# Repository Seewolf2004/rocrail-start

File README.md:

# rocrail-start
startet Rocrail auf einem Raspberry Pi 4B

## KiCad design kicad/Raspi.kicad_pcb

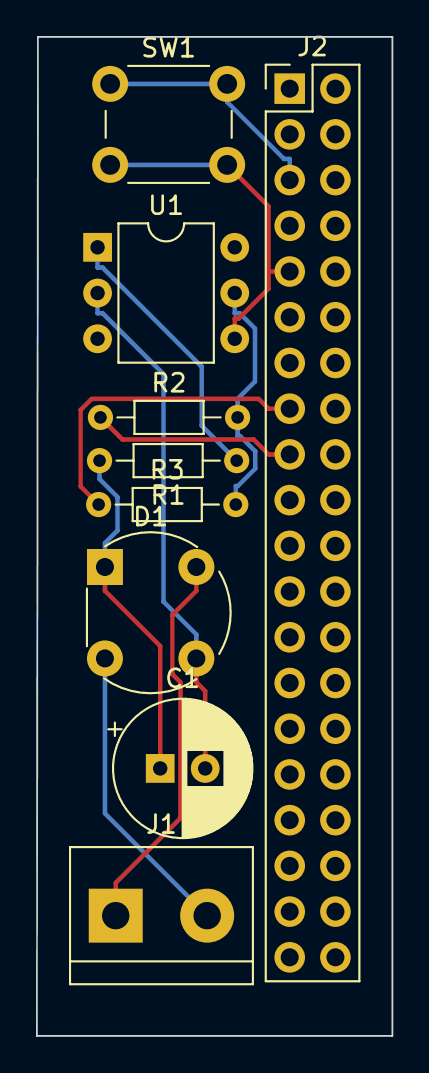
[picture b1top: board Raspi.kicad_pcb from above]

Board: 2 copper layers, 19.8 x 55.5 mm, 9 parts (0 on the bottom side), 10 nets.

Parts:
C1: 47 uF; CP_Radial_D7.5mm_P2.50mm
D1: D_Bridge_+A-A; Diode_Bridge_Round_D8.9mm
J1: Conn_01x02_Male; TerminalBlock_bornier-2_P5.08mm
J2: Raspberry_Pi_2_3; PinHeader_2x20_P2.54mm_Vertical
R1: 1,5k; R_Axial_DIN0204_L3.6mm_D1.6mm_P7.62mm_Horizontal
R2: 10k; R_Axial_DIN0204_L3.6mm_D1.6mm_P7.62mm_Horizontal
R3: 1k; R_Axial_DIN0204_L3.6mm_D1.6mm_P7.62mm_Horizontal
SW1: SW_Push; SW_PUSH_6mm_H4.3mm
U1: CNY17-4; DIP-6_W7.62mm

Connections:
/GPIO3: J2.5, SW1.1
unnamed: C1.1, D1.1, R1.2
unnamed: C1.2, D1.3, U1.2
unnamed: D1.2, J1.2
unnamed: D1.4, J1.1
unnamed: J2.9, SW1.2, U1.4
unnamed: J2.15, R3.1
unnamed: J2.17, R2.1
unnamed: R1.1, U1.1
unnamed: R2.2, R3.2, U1.5

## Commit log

2020-06-07 Start Python2 Script
2020-06-07 /etc/init.d/rocraild
    from https://www.wiwi.uni-bonn.de/middelhauve/raspiweb/
2020-06-07 Create crontab
2020-06-07 Create root Crontab
2020-06-07 Rename readme to readme.md
2020-06-08 syslog hinzugefügt
